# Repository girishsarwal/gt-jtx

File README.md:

# gt-jtx
What is gt-jtx?
I feel it's cool to control an airplane with a 3d joystick rather than gimbals. It's intuitive and real aircraft pilots (or those trained on MSFS) can appreciate. See Yoke and HOTAS ("Hotass")

After a good amount of self provocation, I embarked on the journey of doing a joystick based 4 analog and 1 digital channels transmitter for controlling Airplanes. Additionally, this system needs to have a basic menu system, settings (Expo/Dr, Rev etc..) and a monitor

# How does it work?
The gt-jtx uses a 3d joystick for controlling an RC airplane. The X axis map to ailerons (roll), Y to Elevator (pitch) and the joystick grip twist/Z axis map to Rudder (Yaw) control. The throttle control has a separate pot on the base of the joystick. Digital push buttons 5-12 on the joystick base are trim switches for the four channels and pressing unique combos on these switches along with power switch navigates through the menu and settings screen.

# Variants
There are three variants of the gt-jtx in order of ease of development

- Arduino Mega - V1.2 available - Open TX
- ATMEGA 8 - V1.0 available - Custom firmware
- ATMEGA 32 - Work under progress

See the wiki for more details

# Disclaimer
I take no responsibility or warranty for any damage to you or your equipment, that may arise out of or is a consequence of using or reproducing any parts or features of the gt-jtx software/hardware system. Everything you do is completely at your own risk and expense.

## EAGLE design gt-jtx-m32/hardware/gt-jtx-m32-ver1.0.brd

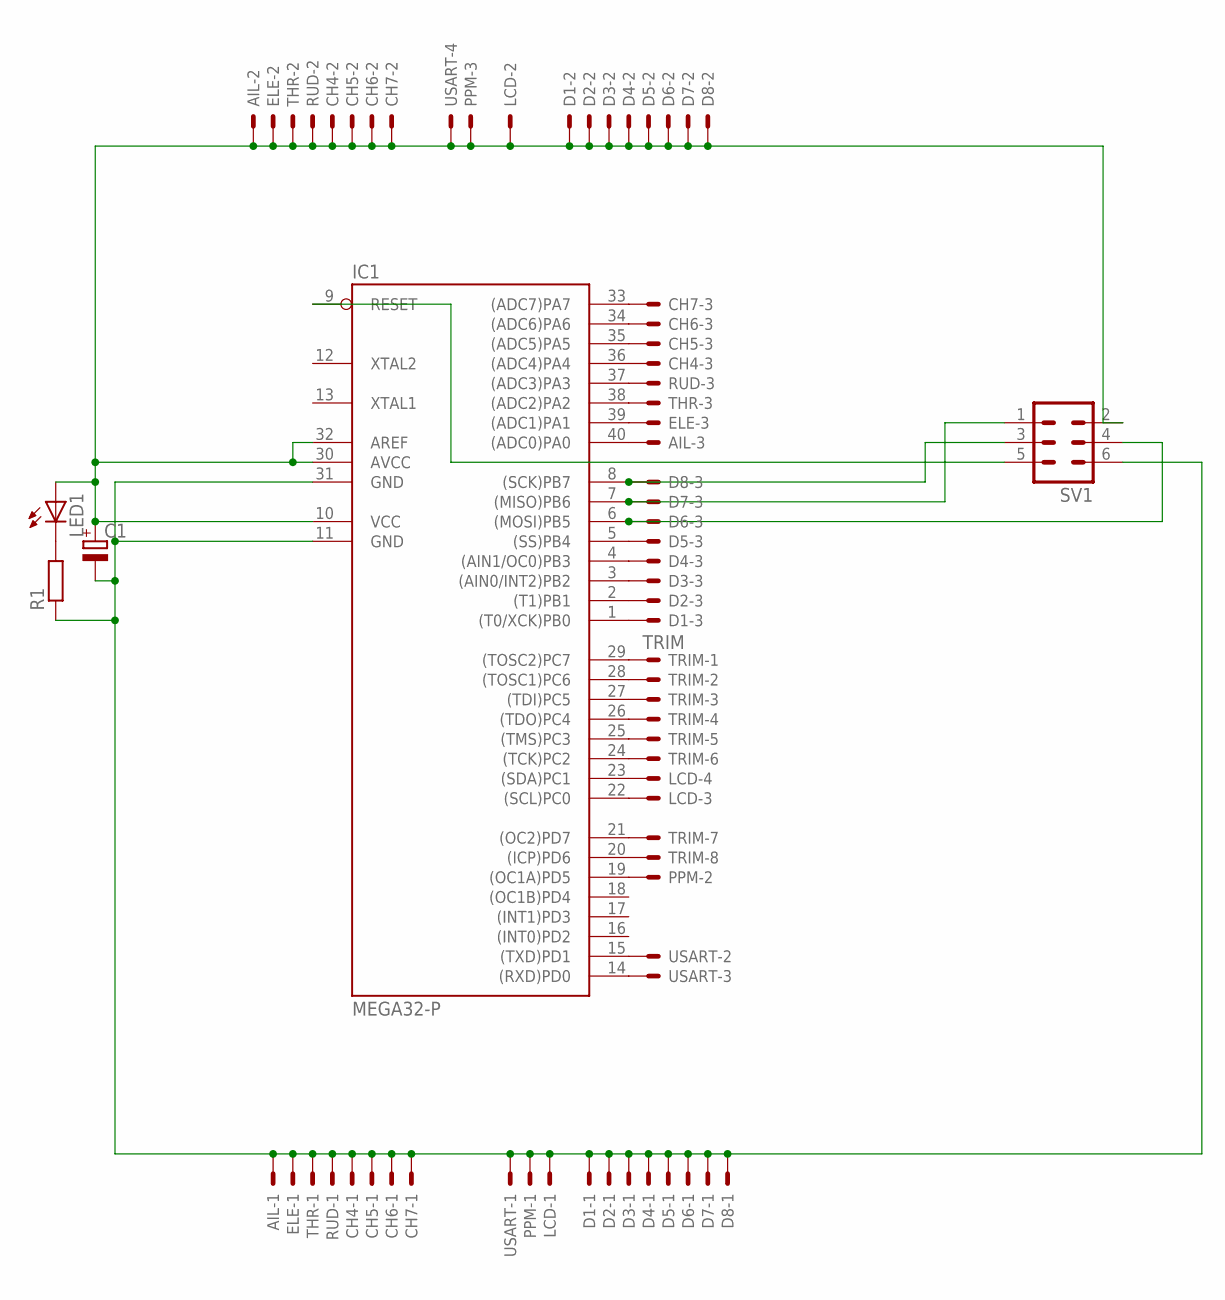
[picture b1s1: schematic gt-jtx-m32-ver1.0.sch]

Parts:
AIL: JST-XH-03-PIN-LONG-PAD; JST-XH-03-PACKAGE-LONG-PAD
C1: CPOL-EUC; PANASONIC_C
CH4, CH5, CH6, CH7: JST-XH-03-PIN-LONG-PAD; JST-XH-03-PACKAGE-LONG-PAD
D1, D2, D3, D4, D5, D6, D7, D8: JST-XH-03-PIN-LONG-PAD; JST-XH-03-PACKAGE-LONG-PAD
ELE: JST-XH-03-PIN-LONG-PAD; JST-XH-03-PACKAGE-LONG-PAD
IC1: MEGA32-P; DIL40
LCD: JST-XH-04-PIN-LONG-PAD; JST-XH-04-PACKAGE-LONG-PAD
LED1: LED5MM
PPM: JST-XH-03-PIN-LONG-PAD; JST-XH-03-PACKAGE-LONG-PAD
R1: R0204/7; 0204/7
RUD: JST-XH-03-PIN-LONG-PAD; JST-XH-03-PACKAGE-LONG-PAD
SV1: MA03-2
THR: JST-XH-03-PIN-LONG-PAD; JST-XH-03-PACKAGE-LONG-PAD
TRIM: TRIM; JST-XH-08-PACKAGE-LONG-PAD
USART: JST-XH-04-PIN-LONG-PAD; JST-XH-04-PACKAGE-LONG-PAD

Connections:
GND: AIL.1, C1.-, CH4.1, CH5.1, CH6.1, CH7.1, D1.1, D2.1, D3.1, D4.1, D5.1, D6.1, D7.1, D8.1, ELE.1, IC1.11 (GND), IC1.31 (GND), LCD.1, PPM.1, R1.1, RUD.1, SV1.6, THR.1, USART.1
unnamed: CH5.3, IC1.35 ((ADC5)PA5)
unnamed: CH6.3, IC1.34 ((ADC6)PA6)
unnamed: IC1.29 ((TOSC2)PC7), TRIM.1
unnamed: IC1.28 ((TOSC1)PC6), TRIM.2
unnamed: D1.3, IC1.1 ((T0/XCK)PB0)
unnamed: IC1.15 ((TXD)PD1), USART.2
unnamed: IC1.27 ((TDI)PC5), TRIM.3
unnamed: IC1.26 ((TDO)PC4), TRIM.4
unnamed: IC1.9 (RESET), SV1.5
unnamed: IC1.25 ((TMS)PC3), TRIM.5
unnamed: IC1.24 ((TCK)PC2), TRIM.6
unnamed: D6.3, IC1.6 ((MOSI)PB5), SV1.4
unnamed: D7.3, IC1.7 ((MISO)PB6), SV1.1
unnamed: D8.3, IC1.8 ((SCK)PB7), SV1.3
unnamed: D2.3, IC1.2 ((T1)PB1)
unnamed: IC1.21 ((OC2)PD7), TRIM.7
unnamed: IC1.20 ((ICP)PD6), TRIM.8
unnamed: IC1.14 ((RXD)PD0), USART.3
unnamed: IC1.23 ((SDA)PC1), LCD.4
unnamed: CH7.3, IC1.33 ((ADC7)PA7)
unnamed: CH4.3, IC1.36 ((ADC4)PA4)
unnamed: IC1.22 ((SCL)PC0), LCD.3
unnamed: IC1.19 ((OC1A)PD5), PPM.2
unnamed: D3.3, IC1.3 ((AIN0/INT2)PB2)
unnamed: D4.3, IC1.4 ((AIN1/OC0)PB3)
unnamed: D5.3, IC1.5 ((SS)PB4)
unnamed: IC1.37 ((ADC3)PA3), RUD.3
unnamed: IC1.38 ((ADC2)PA2), THR.3
unnamed: ELE.3, IC1.39 ((ADC1)PA1)
unnamed: AIL.3, IC1.40 ((ADC0)PA0)
unnamed: LED1.K (C), R1.2
VCC: AIL.2, C1.+, CH4.2, CH5.2, CH6.2, CH7.2, D1.2, D2.2, D3.2, D4.2, D5.2, D6.2, D7.2, D8.2, ELE.2, IC1.10 (VCC), IC1.30 (AVCC), IC1.32 (AREF), LCD.2, LED1.A, PPM.3, RUD.2, SV1.2, THR.2, USART.4

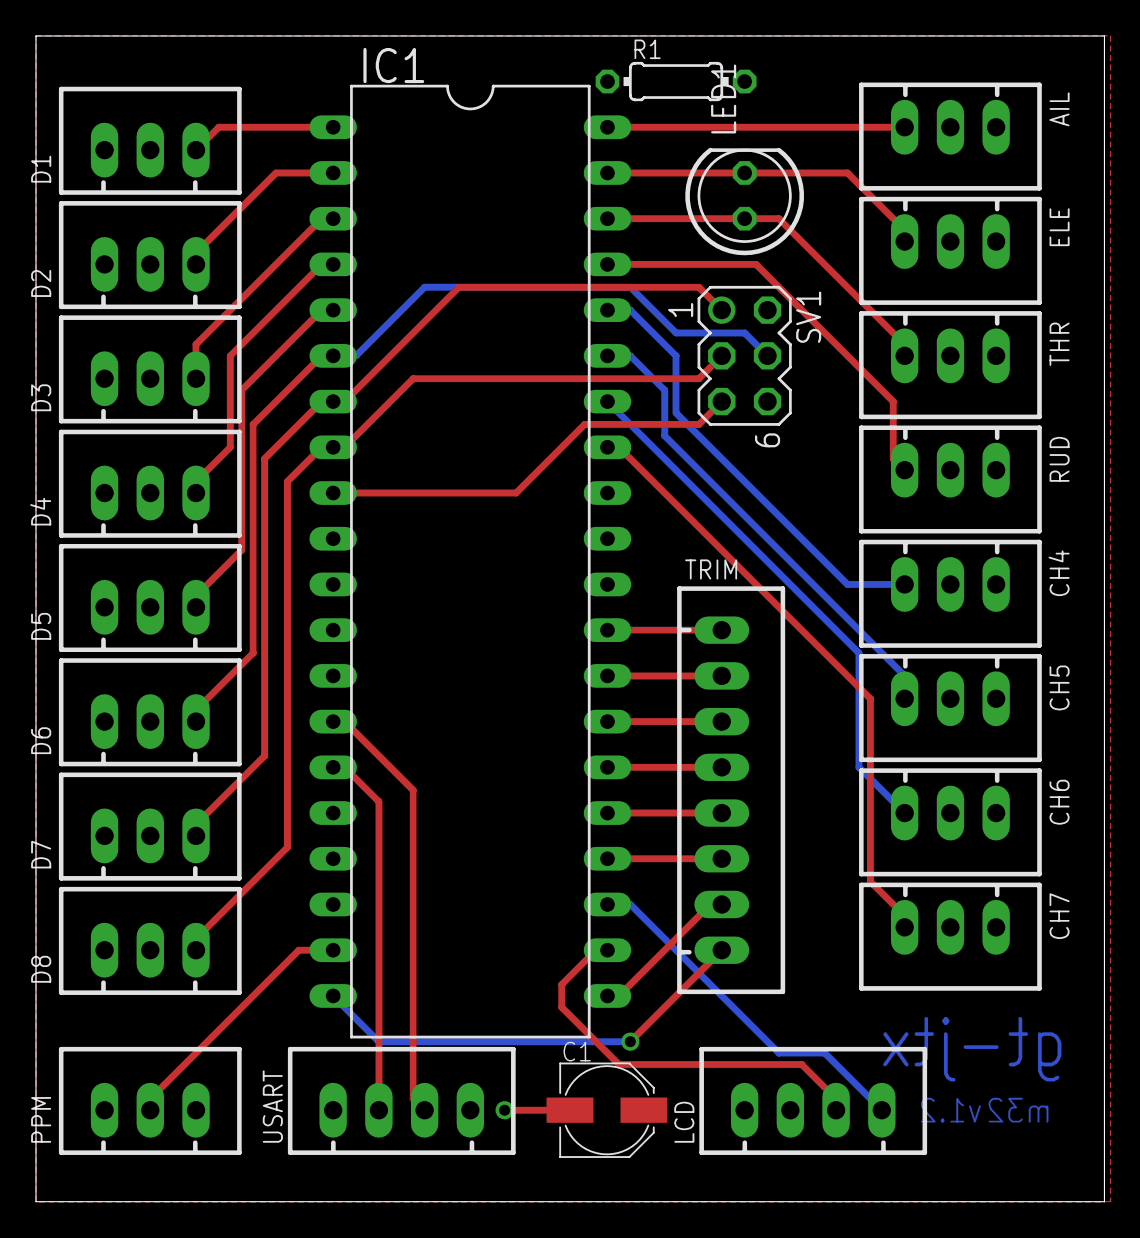
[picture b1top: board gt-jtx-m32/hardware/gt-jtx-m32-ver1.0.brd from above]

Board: 2 copper layers, 59.4 x 64.8 mm, 25 parts (0 on the bottom side), 33 nets.

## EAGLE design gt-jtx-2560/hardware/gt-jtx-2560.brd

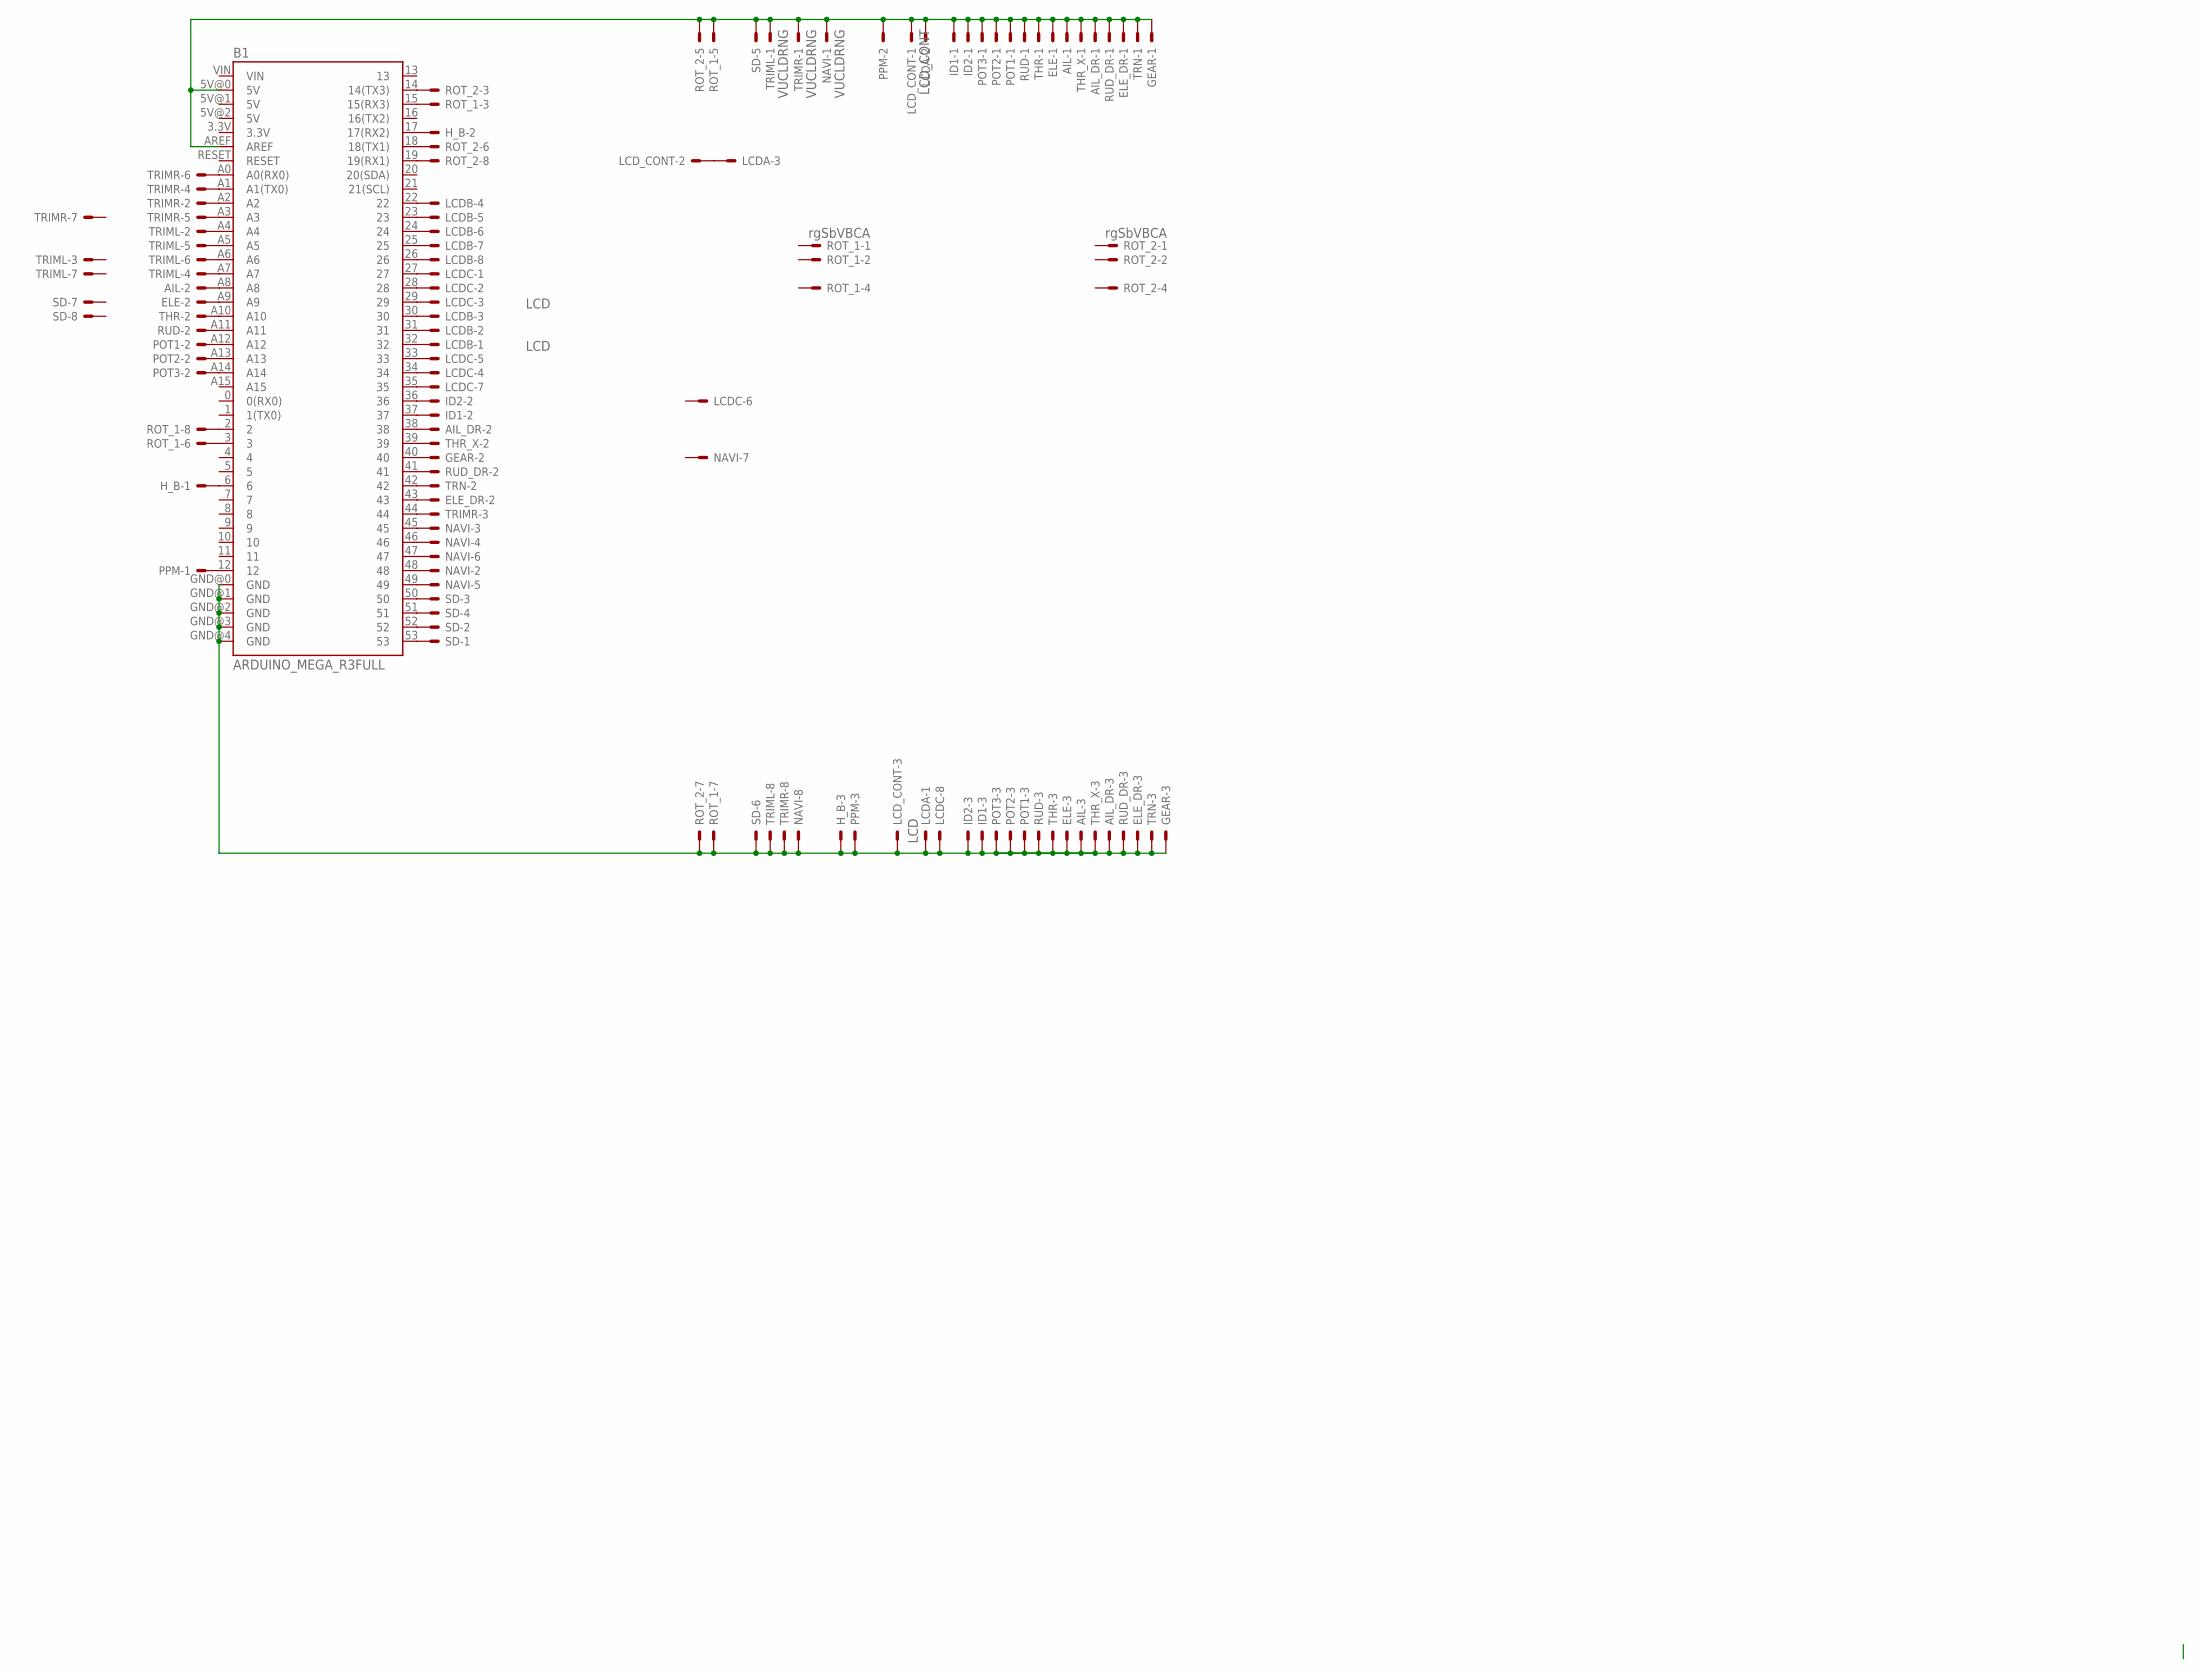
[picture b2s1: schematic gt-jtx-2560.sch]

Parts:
AIL: JST-XH-03-PIN-LONG-PAD; JST-XH-03-PACKAGE-LONG-PAD
AIL_DR: JST-XH-03-PIN-LONG-PAD; JST-XH-03-PACKAGE-LONG-PAD
B1: ARDUINO_MEGA_R3FULL; ARDUINO_MEGA
ELE: JST-XH-03-PIN-LONG-PAD; JST-XH-03-PACKAGE-LONG-PAD
ELE_DR: JST-XH-03-PIN-LONG-PAD; JST-XH-03-PACKAGE-LONG-PAD
GEAR: JST-XH-03-PIN-LONG-PAD; JST-XH-03-PACKAGE-LONG-PAD
H_B: JST-XH-03-PIN-LONG-PAD; JST-XH-03-PACKAGE-LONG-PAD
ID1, ID2: JST-XH-03-PIN-LONG-PAD; JST-XH-03-PACKAGE-LONG-PAD
LCDA: LCD; JST-XH-03-PACKAGE-LONG-PAD
LCDB: LCD; JST-XH-08-PACKAGE-LONG-PAD
LCDC: LCD; JST-XH-08-PACKAGE-LONG-PAD
LCD_CONT: LCD_CONT; JST-XH-03-PACKAGE-LONG-PAD
NAVI: VUCLDRNG; JST-XH-08-PACKAGE-LONG-PAD
POT1, POT2, POT3: JST-XH-03-PIN-LONG-PAD; JST-XH-03-PACKAGE-LONG-PAD
PPM: JST-XH-03-PIN-LONG-PAD; JST-XH-03-PACKAGE-LONG-PAD
ROT_1, ROT_2: rgSbVBCA; JST-XH-08-PACKAGE-LONG-PAD
RUD: JST-XH-03-PIN-LONG-PAD; JST-XH-03-PACKAGE-LONG-PAD
RUD_DR: JST-XH-03-PIN-LONG-PAD; JST-XH-03-PACKAGE-LONG-PAD
SD: JST-XH-08-PIN-LONG-PAD; JST-XH-08-PACKAGE-LONG-PAD
THR: JST-XH-03-PIN-LONG-PAD; JST-XH-03-PACKAGE-LONG-PAD
THR_X: JST-XH-03-PIN-LONG-PAD; JST-XH-03-PACKAGE-LONG-PAD
TRIML: VUCLDRNG; JST-XH-08-PACKAGE-LONG-PAD
TRIMR: VUCLDRNG; JST-XH-08-PACKAGE-LONG-PAD
TRN: JST-XH-03-PIN-LONG-PAD; JST-XH-03-PACKAGE-LONG-PAD

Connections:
GND: AIL.3, AIL_DR.3, B1.GND@0 (GND), B1.GND@1 (GND), B1.GND@2 (GND), B1.GND@3 (GND), B1.GND@4 (GND), ELE.3, ELE_DR.3, GEAR.3, H_B.3, ID1.3, ID2.3, LCDA.1, LCDC.8, LCD_CONT.3, NAVI.8, POT1.3, POT2.3, POT3.3, PPM.3, ROT_1.7, ROT_2.7, RUD.3, RUD_DR.3, SD.6, THR.3, THR_X.3, TRIML.8, TRIMR.8, TRN.3; also elsewhere on the board
unnamed: B1.22, LCDB.4
unnamed: B1.23, LCDB.5
unnamed: B1.24, LCDB.6
unnamed: B1.25, LCDB.7
unnamed: B1.26, LCDB.8
unnamed: B1.27, LCDC.1
unnamed: B1.28, LCDC.2
unnamed: B1.29, LCDC.3
unnamed: B1.48, NAVI.2
unnamed: B1.45, NAVI.3
unnamed: B1.46, NAVI.4
unnamed: B1.49, NAVI.5
unnamed: B1.47, NAVI.6
unnamed: B1.A2, TRIMR.2
unnamed: B1.A7, TRIML.4
unnamed: B1.53, SD.1
unnamed: B1.A5, TRIML.5
unnamed: B1.44, TRIMR.3
unnamed: AIL.2, B1.A8
unnamed: B1.A9, ELE.2
unnamed: B1.A10, THR.2
unnamed: B1.A11, RUD.2
unnamed: B1.A12, POT1.2
unnamed: B1.A13, POT2.2
unnamed: B1.A14, POT3.2
unnamed: B1.52, SD.2
unnamed: B1.A1 (A1(TX0)), TRIMR.4
unnamed: B1.A3, TRIMR.5
unnamed: B1.50, SD.3
unnamed: B1.51, SD.4
unnamed: B1.15 (15(RX3)), ROT_1.3
unnamed: B1.6, H_B.1
unnamed: B1.39, THR_X.2
unnamed: B1.41, RUD_DR.2
unnamed: B1.43, ELE_DR.2
unnamed: AIL_DR.2, B1.38
unnamed: B1.42, TRN.2
unnamed: B1.40, GEAR.2
unnamed: B1.17 (17(RX2)), H_B.2
unnamed: B1.A0 (A0(RX0)), TRIMR.6
unnamed: B1.30, LCDB.3
unnamed: B1.31, LCDB.2
unnamed: B1.A6, TRIML.6
unnamed: B1.A4, TRIML.2
unnamed: B1.14 (14(TX3)), ROT_2.3
unnamed: B1.2, ROT_1.8
unnamed: B1.3, ROT_1.6
unnamed: B1.19 (19(RX1)), ROT_2.8
unnamed: B1.18 (18(TX1)), ROT_2.6
unnamed: B1.32, LCDB.1
unnamed: B1.34, LCDC.4
unnamed: B1.33, LCDC.5
unnamed: B1.35, LCDC.7
unnamed: LCDA.3, LCD_CONT.2
unnamed: B1.36, ID2.2
unnamed: B1.37, ID1.2
VCC: AIL.1, AIL_DR.1, B1.5V@0 (5V), B1.AREF, ELE.1, ELE_DR.1, GEAR.1, ID1.1, ID2.1, LCDA.2, LCD_CONT.1, NAVI.1, POT1.1, POT2.1, POT3.1, PPM.2, ROT_1.5, ROT_2.5, RUD.1, RUD_DR.1, SD.5, THR.1, THR_X.1, TRIML.1, TRIMR.1, TRN.1

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
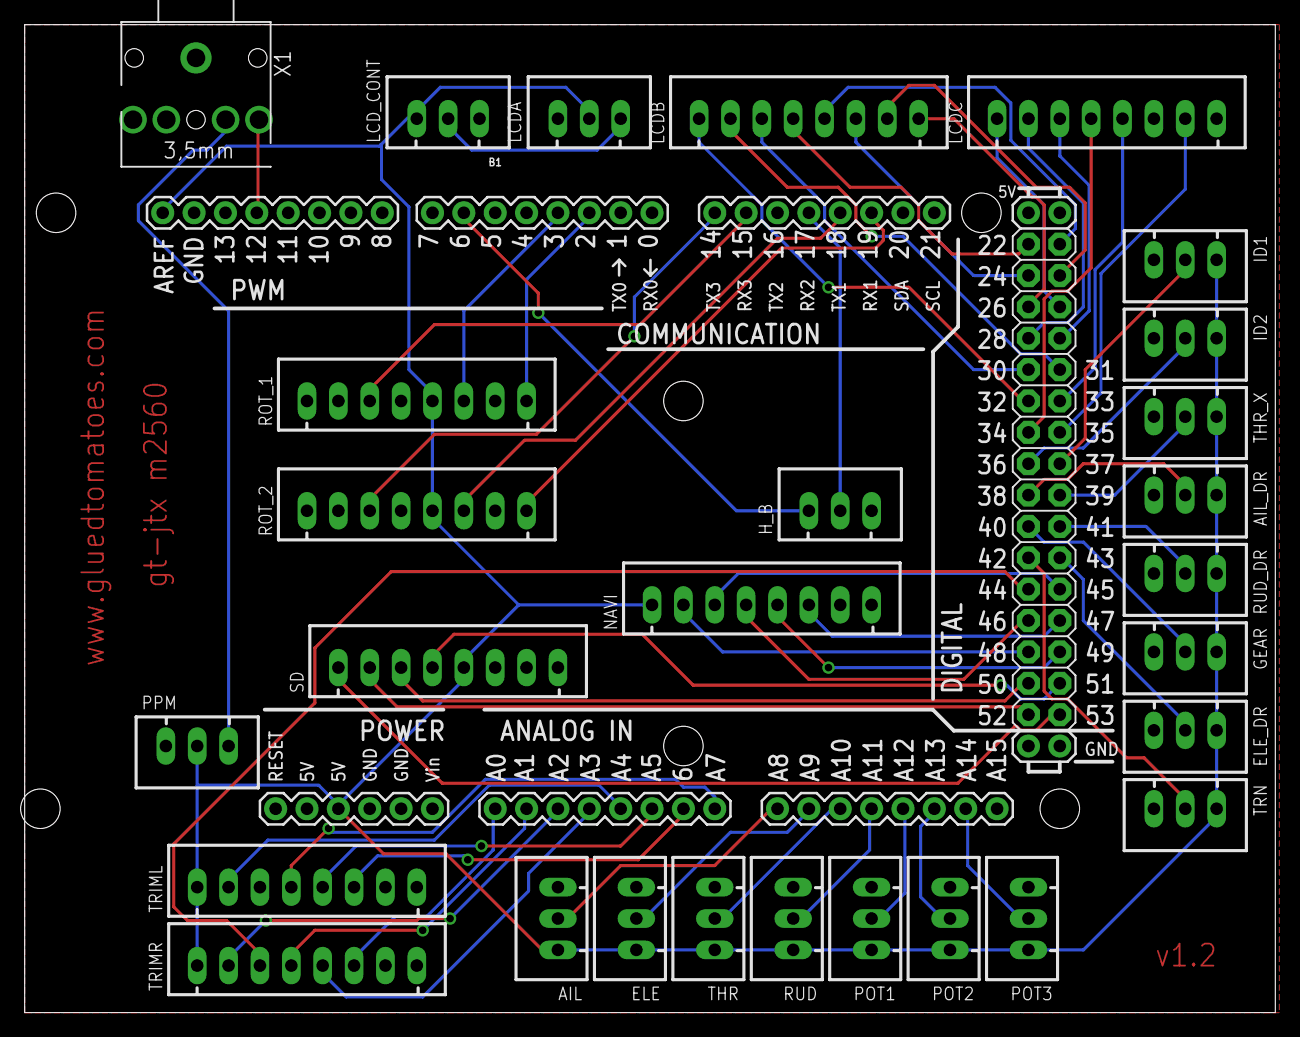
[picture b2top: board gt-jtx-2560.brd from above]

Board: 2 copper layers, 101.3 x 80.0 mm, 29 parts (0 on the bottom side), 60 nets.

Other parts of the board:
X1: SIM; STX3100

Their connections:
GND: X1.1; also elsewhere on the board

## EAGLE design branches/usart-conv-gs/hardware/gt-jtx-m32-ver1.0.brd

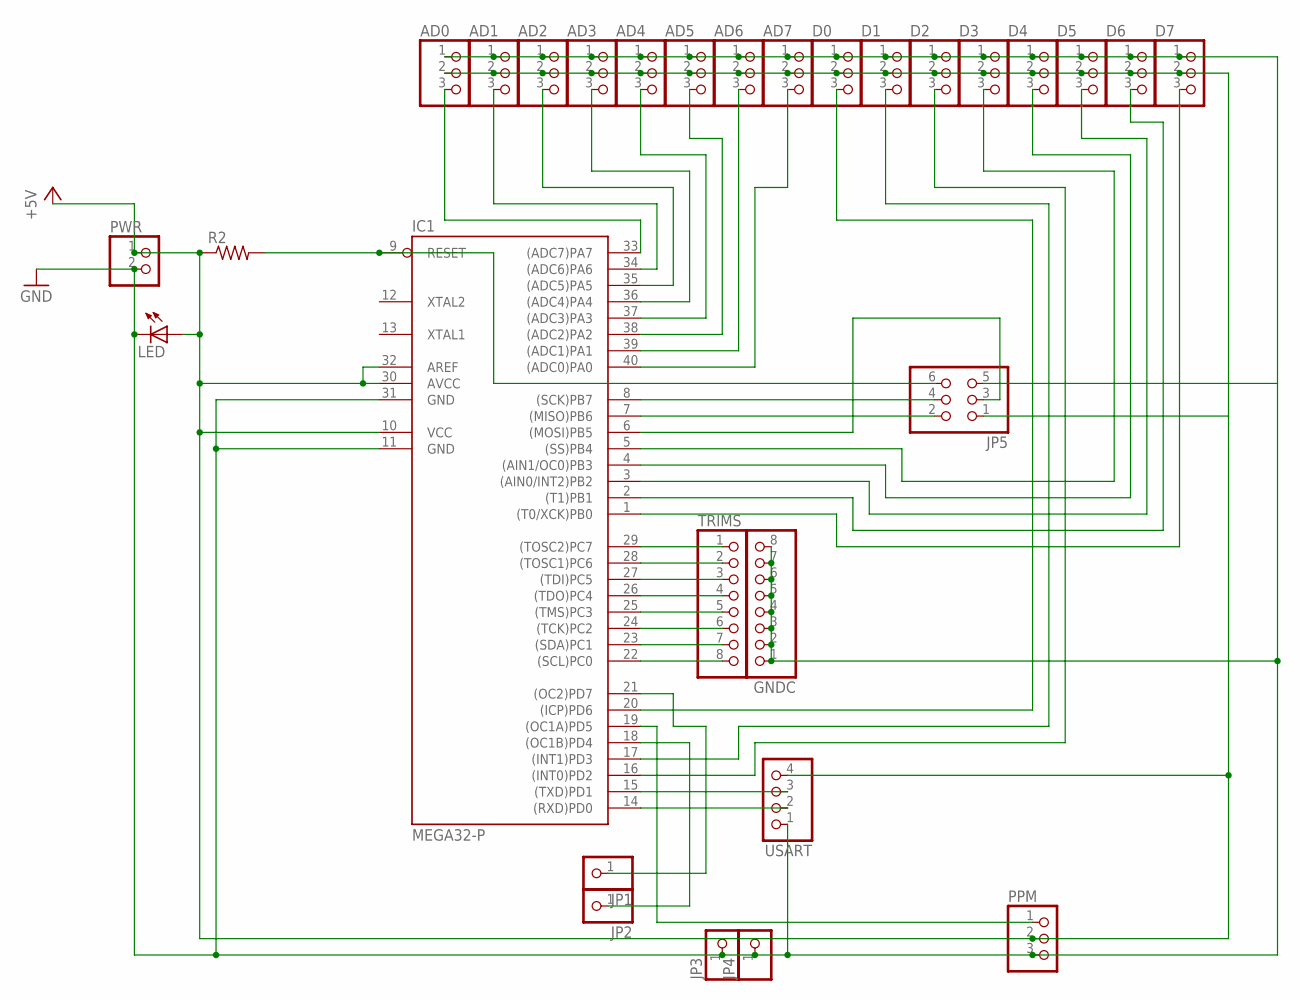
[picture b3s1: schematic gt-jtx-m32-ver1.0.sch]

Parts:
AD0, AD1, AD2, AD3, AD4, AD5, AD6, AD7: PINHD-1X3; 1X03
D0, D1, D2, D3, D4, D5, D6, D7: PINHD-1X3; 1X03
GNDC: PINHD-1X8; 1X08
IC1: MEGA32-P; DIL40
JP1, JP2, JP3, JP4: PINHD-1X1; 1X01
JP5: PINHD-2X3; 2X03
LED: LED5MM
PPM: PINHD-1X3; 1X03
PWR: PINHD-1X2; 1X02
R2: R-US_0204/2V; 0204V
TRIMS: PINHD-1X8; 1X08
USART: PINHD-1X4; 1X04

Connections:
+5V: AD0.2, AD1.2, AD2.2, AD3.2, AD4.2, AD5.2, AD6.2, AD7.2, D0.2, D1.2, D2.2, D3.2, D4.2, D5.2, D6.2, D7.2, IC1.10 (VCC), IC1.30 (AVCC), IC1.32 (AREF), JP5.1, LED.A, PPM.2, PWR.1, R2.1, USART.4
GND: AD0.1, AD1.1, AD2.1, AD3.1, AD4.1, AD5.1, AD6.1, AD7.1, D0.1, D1.1, D2.1, D3.1, D4.1, D5.1, D6.1, D7.1, GNDC.1, GNDC.2, GNDC.3, GNDC.4, GNDC.5, GNDC.6, GNDC.7, GNDC.8, IC1.11 (GND), IC1.31 (GND), JP3.1, JP4.1, JP5.5, LED.K (C), PPM.3, PWR.2, USART.1
unnamed: AD7.3, IC1.40 ((ADC0)PA0)
unnamed: AD6.3, IC1.39 ((ADC1)PA1)
unnamed: AD5.3, IC1.38 ((ADC2)PA2)
unnamed: AD4.3, IC1.37 ((ADC3)PA3)
unnamed: IC1.14 ((RXD)PD0), USART.2
unnamed: IC1.15 ((TXD)PD1), USART.3
unnamed: IC1.29 ((TOSC2)PC7), TRIMS.1
unnamed: AD3.3, IC1.36 ((ADC4)PA4)
unnamed: IC1.9 (RESET), JP5.6, R2.2
unnamed: AD2.3, IC1.35 ((ADC5)PA5)
unnamed: AD1.3, IC1.34 ((ADC6)PA6)
unnamed: IC1.6 ((MOSI)PB5), JP5.3
unnamed: IC1.7 ((MISO)PB6), JP5.2
unnamed: IC1.8 ((SCK)PB7), JP5.4
unnamed: IC1.19 ((OC1A)PD5), PPM.1
unnamed: IC1.28 ((TOSC1)PC6), TRIMS.2
unnamed: AD0.3, IC1.33 ((ADC7)PA7)
unnamed: IC1.27 ((TDI)PC5), TRIMS.3
unnamed: IC1.26 ((TDO)PC4), TRIMS.4
unnamed: IC1.25 ((TMS)PC3), TRIMS.5
unnamed: IC1.24 ((TCK)PC2), TRIMS.6
unnamed: IC1.23 ((SDA)PC1), TRIMS.7
unnamed: IC1.22 ((SCL)PC0), TRIMS.8
unnamed: D3.3, IC1.5 ((SS)PB4)
unnamed: D4.3, IC1.4 ((AIN1/OC0)PB3)
unnamed: D5.3, IC1.3 ((AIN0/INT2)PB2)
unnamed: D6.3, IC1.2 ((T1)PB1)
unnamed: D7.3, IC1.1 ((T0/XCK)PB0)
unnamed: D2.3, IC1.16 ((INT0)PD2)
unnamed: D1.3, IC1.17 ((INT1)PD3)
unnamed: D0.3, IC1.20 ((ICP)PD6)
unnamed: IC1.18 ((OC1B)PD4), JP2.1
unnamed: IC1.21 ((OC2)PD7), JP1.1

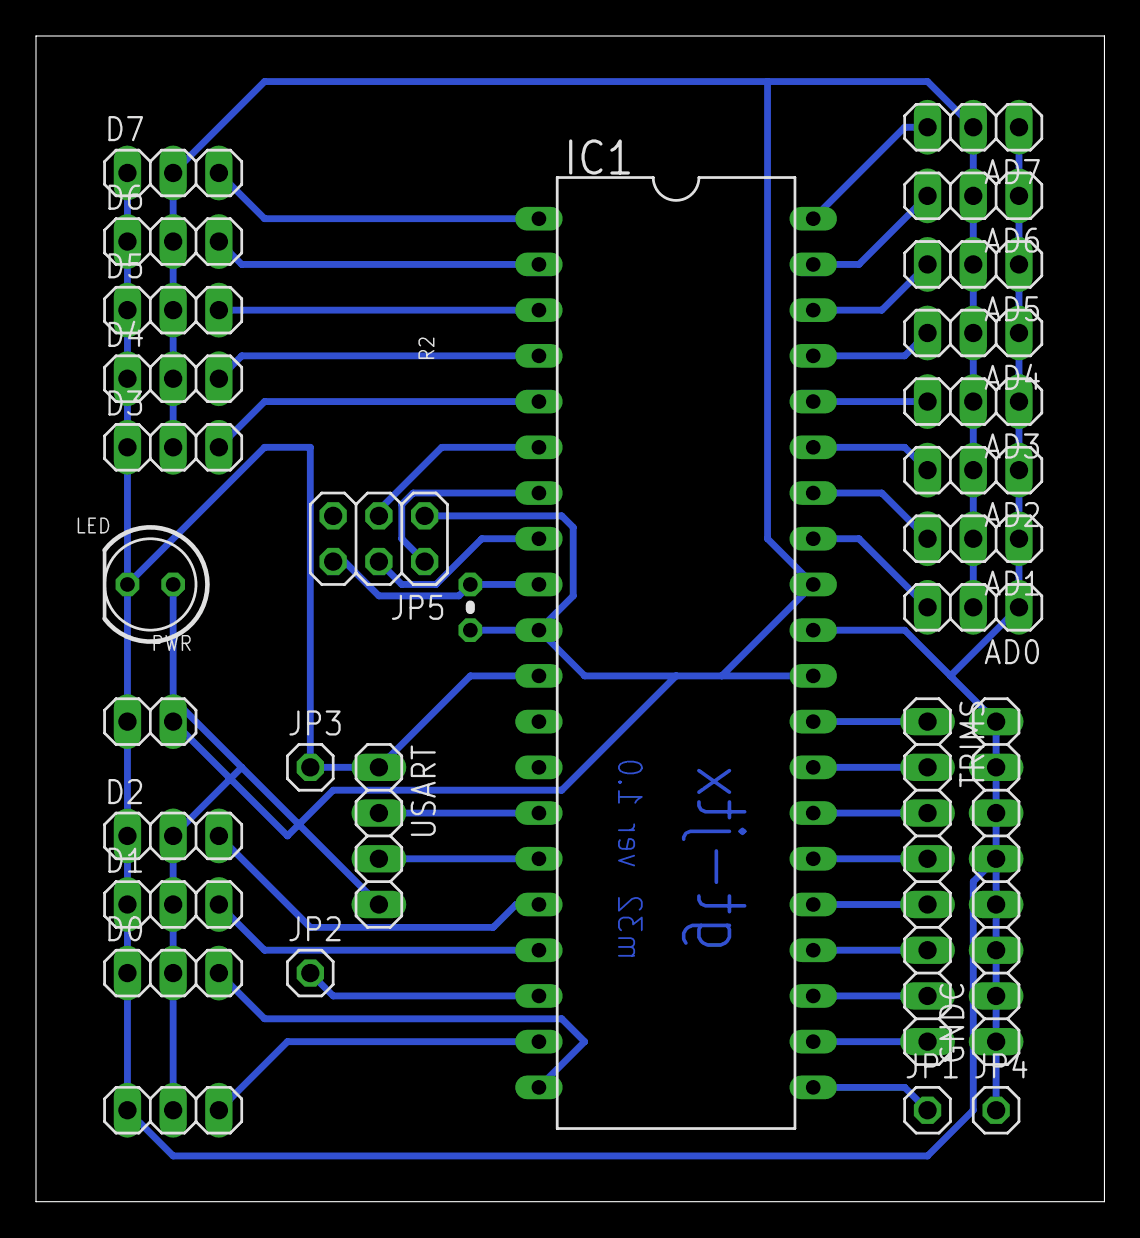
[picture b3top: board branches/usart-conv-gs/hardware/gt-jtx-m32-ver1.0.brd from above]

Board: 2 copper layers, 59.4 x 64.8 mm, 29 parts (0 on the bottom side), 35 nets.

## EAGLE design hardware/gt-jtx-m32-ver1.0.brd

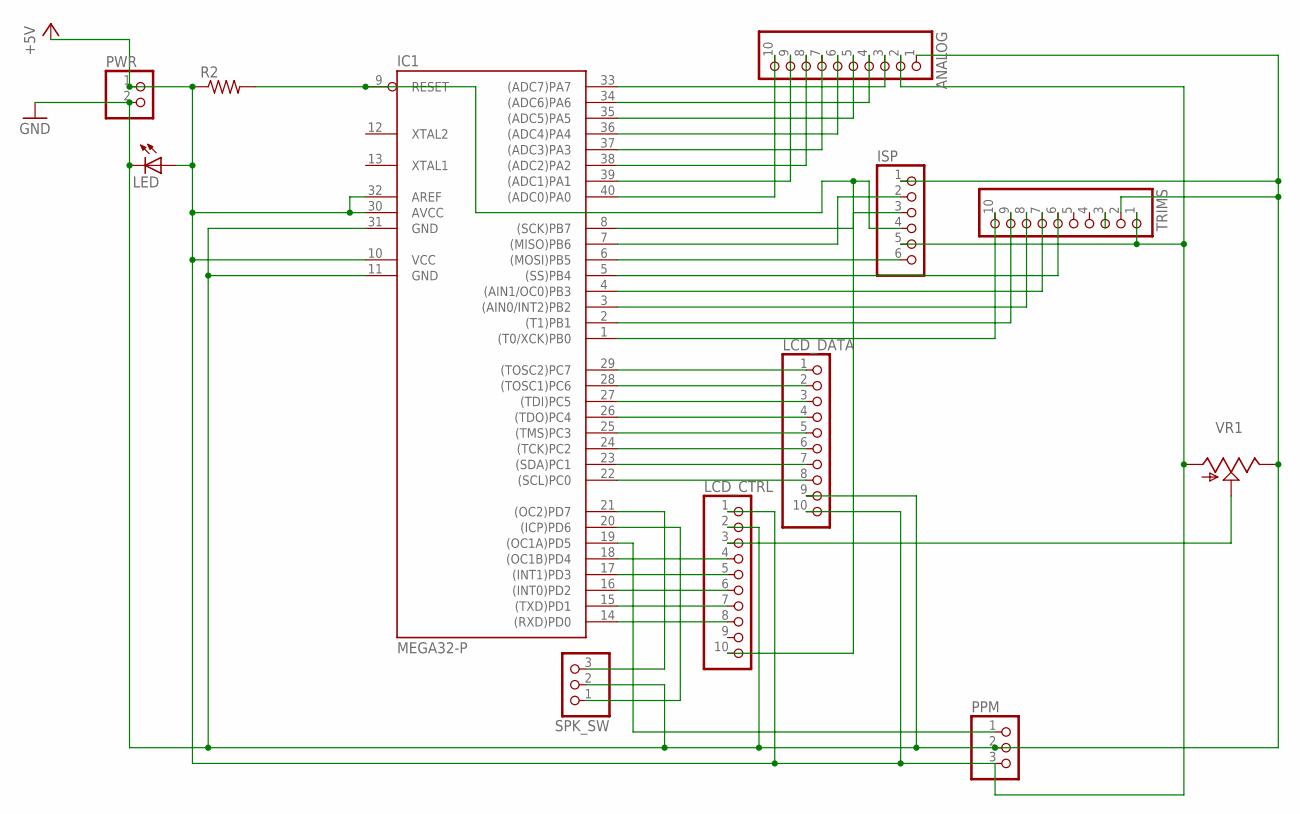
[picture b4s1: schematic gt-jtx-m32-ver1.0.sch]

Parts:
ANALOG: PINHD-1X10; 1X10
IC1: MEGA32-P; DIL40
ISP: PINHD-1X6; 1X06
LCD_CTRL: PINHD-1X10; 1X10
LCD_DATA: PINHD-1X10; 1X10
LED: LED5MM
PPM: PINHD-1X3; 1X03
PWR: PINHD-1X2; 1X02
R2: R-US_0204/2V; 0204V
SPK_SW: PINHD-1X3; 1X03
TRIMS: PINHD-1X10; 1X10
VR1: TRIM_US-CA6V; CA6V

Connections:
+5V: ANALOG.2, IC1.10 (VCC), IC1.30 (AVCC), IC1.32 (AREF), ISP.5, LCD_CTRL.1, LCD_DATA.10, LED.A, PPM.3, PWR.1, R2.1, TRIMS.1, VR1.A
CONTRA_ADJ: LCD_CTRL.3, VR1.S
CS1: IC1.17 ((INT1)PD3), LCD_CTRL.5
CS2: IC1.18 ((OC1B)PD4), LCD_CTRL.4
D0: IC1.22 ((SCL)PC0), LCD_DATA.8
D1: IC1.23 ((SDA)PC1), LCD_DATA.7
D2: IC1.24 ((TCK)PC2), LCD_DATA.6
D3: IC1.25 ((TMS)PC3), LCD_DATA.5
D4: IC1.26 ((TDO)PC4), LCD_DATA.4
D5: IC1.27 ((TDI)PC5), LCD_DATA.3
D6: IC1.28 ((TOSC1)PC6), LCD_DATA.2
D7: IC1.29 ((TOSC2)PC7), LCD_DATA.1
E: IC1.16 ((INT0)PD2), LCD_CTRL.6
GND: ANALOG.1, IC1.11 (GND), IC1.31 (GND), ISP.1, LCD_CTRL.2, LCD_DATA.9, LED.K (C), PPM.2, PWR.2, SPK_SW.2, TRIMS.2, VR1.E
unnamed: ANALOG.10, IC1.40 ((ADC0)PA0)
unnamed: ANALOG.9, IC1.39 ((ADC1)PA1)
unnamed: ANALOG.8, IC1.38 ((ADC2)PA2)
unnamed: ANALOG.7, IC1.37 ((ADC3)PA3)
unnamed: IC1.20 ((ICP)PD6), SPK_SW.1
unnamed: IC1.21 ((OC2)PD7), SPK_SW.3
unnamed: ANALOG.6, IC1.36 ((ADC4)PA4)
unnamed: IC1.9 (RESET), ISP.4, LCD_CTRL.10, R2.2
unnamed: ANALOG.5, IC1.35 ((ADC5)PA5)
unnamed: ANALOG.4, IC1.34 ((ADC6)PA6)
unnamed: IC1.6 ((MOSI)PB5), ISP.6
unnamed: IC1.7 ((MISO)PB6), ISP.2
unnamed: IC1.8 ((SCK)PB7), ISP.3
unnamed: IC1.19 ((OC1A)PD5), PPM.1
unnamed: ANALOG.3, IC1.33 ((ADC7)PA7)
unnamed: IC1.1 ((T0/XCK)PB0), TRIMS.10
unnamed: IC1.2 ((T1)PB1), TRIMS.9
unnamed: IC1.3 ((AIN0/INT2)PB2), TRIMS.8
unnamed: IC1.4 ((AIN1/OC0)PB3), TRIMS.7
unnamed: IC1.5 ((SS)PB4), TRIMS.6
RS: IC1.14 ((RXD)PD0), LCD_CTRL.8
RW: IC1.15 ((TXD)PD1), LCD_CTRL.7

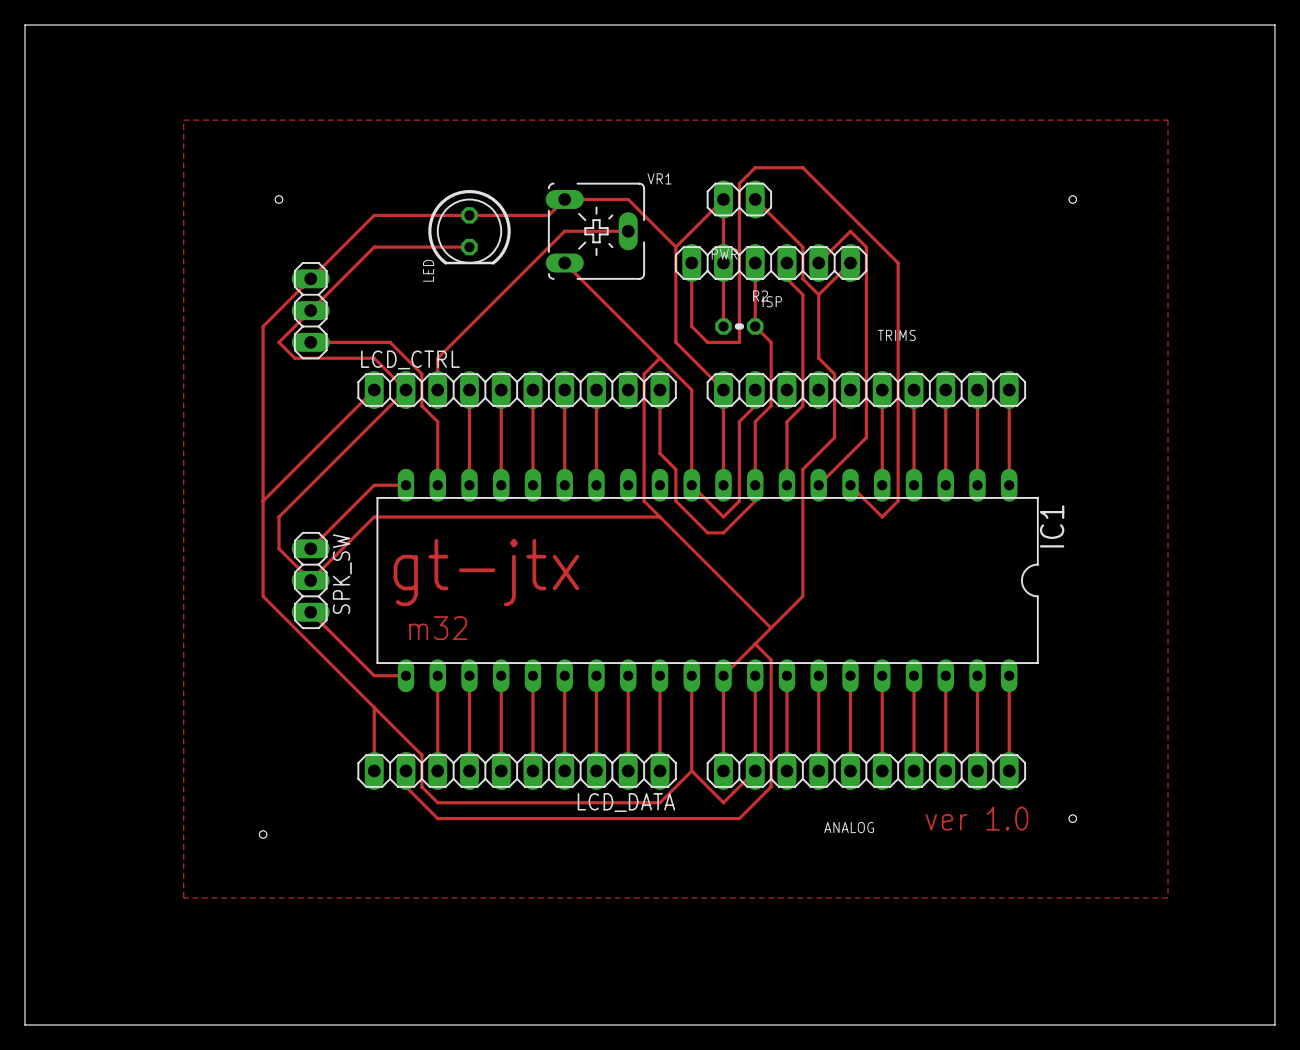
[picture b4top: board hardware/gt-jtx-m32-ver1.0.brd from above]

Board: 2 copper layers, 100.0 x 80.0 mm, 12 parts (0 on the bottom side), 36 nets.

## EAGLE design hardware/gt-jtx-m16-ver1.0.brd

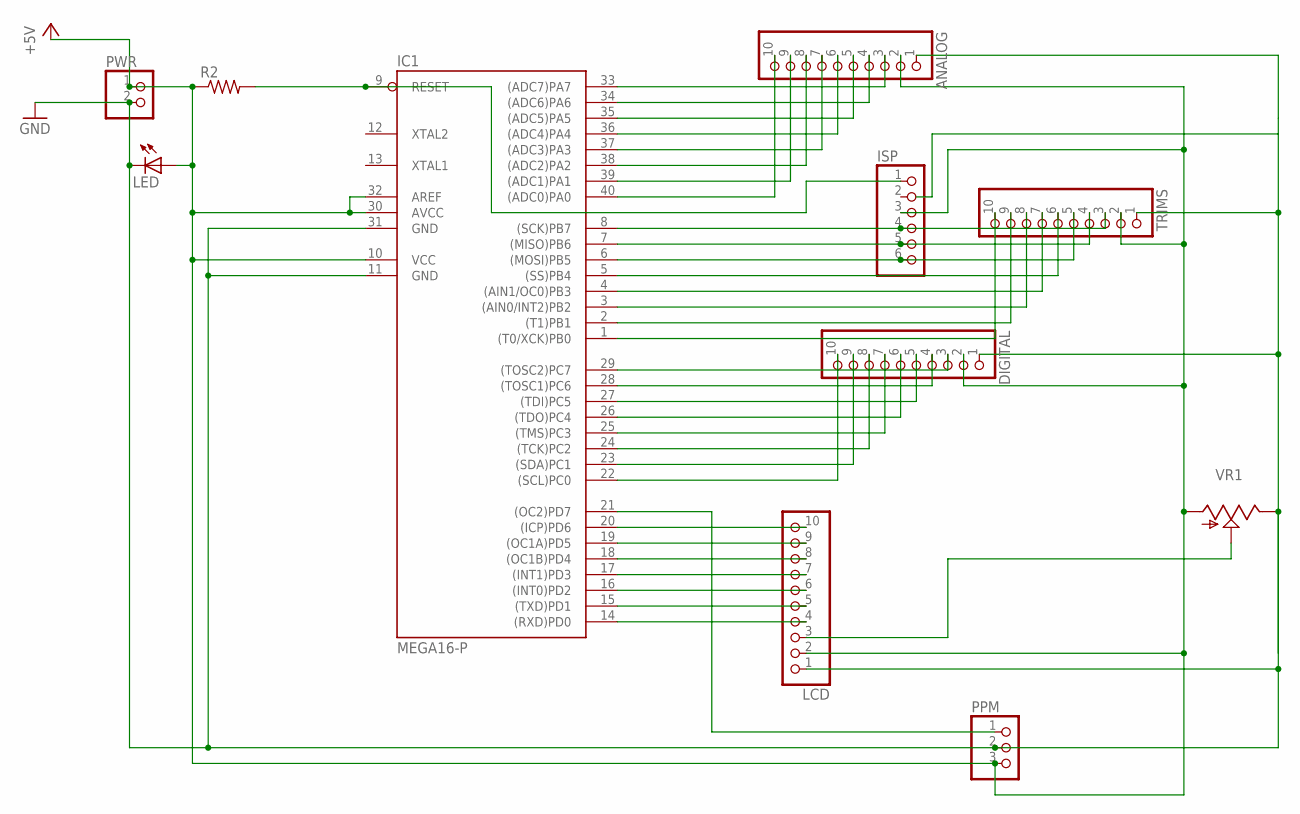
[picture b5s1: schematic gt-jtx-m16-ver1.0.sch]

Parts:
ANALOG: PINHD-1X10; 1X10
DIGITAL: PINHD-1X10; 1X10
IC1: MEGA16-P; DIL40
ISP: PINHD-1X6; 1X06
LCD: PINHD-1X10; 1X10
LED: LED5MM
PPM: PINHD-1X3; 1X03
PWR: PINHD-1X2; 1X02
R2: R-US_0204/2V; 0204V
TRIMS: PINHD-1X10; 1X10
VR1: TRIM_US-CA6V; CA6V

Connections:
+5V: ANALOG.2, DIGITAL.2, IC1.30 (AVCC), IC1.32 (AREF), ISP.3, LCD.2, LED.A, PPM.3, PWR.1, R2.1, TRIMS.2, VR1.A
GND: ANALOG.1, DIGITAL.1, IC1.11 (GND), IC1.31 (GND), LCD.1, LED.K (C), PPM.2, PWR.2, TRIMS.1, VR1.E
unnamed: ANALOG.10, IC1.40 ((ADC0)PA0)
unnamed: ANALOG.9, IC1.39 ((ADC1)PA1)
unnamed: ANALOG.8, IC1.38 ((ADC2)PA2)
unnamed: ANALOG.7, IC1.37 ((ADC3)PA3)
unnamed: IC1.20 ((ICP)PD6), LCD.10
unnamed: IC1.19 ((OC1A)PD5), LCD.9
unnamed: IC1.18 ((OC1B)PD4), LCD.8
unnamed: ANALOG.6, IC1.36 ((ADC4)PA4)
unnamed: LCD.3, VR1.S
unnamed: ANALOG.5, IC1.35 ((ADC5)PA5)
unnamed: ANALOG.4, IC1.34 ((ADC6)PA6)
unnamed: IC1.17 ((INT1)PD3), LCD.7
unnamed: IC1.16 ((INT0)PD2), LCD.6
unnamed: IC1.15 ((TXD)PD1), LCD.5
unnamed: IC1.14 ((RXD)PD0), LCD.4
unnamed: IC1.21 ((OC2)PD7), PPM.1
unnamed: ANALOG.3, IC1.33 ((ADC7)PA7)
unnamed: DIGITAL.3, IC1.29 ((TOSC2)PC7)
unnamed: DIGITAL.4, IC1.28 ((TOSC1)PC6)
unnamed: DIGITAL.5, IC1.27 ((TDI)PC5)
unnamed: DIGITAL.6, IC1.26 ((TDO)PC4)
unnamed: DIGITAL.7, IC1.25 ((TMS)PC3)
unnamed: DIGITAL.8, IC1.24 ((TCK)PC2)
unnamed: DIGITAL.9, IC1.23 ((SDA)PC1)
unnamed: IC1.9 (RESET), ISP.1, R2.2
unnamed: DIGITAL.10, IC1.22 ((SCL)PC0)
unnamed: IC1.1 ((T0/XCK)PB0), TRIMS.10
unnamed: IC1.8 ((SCK)PB7), ISP.4, TRIMS.3
unnamed: IC1.2 ((T1)PB1), TRIMS.9
unnamed: IC1.3 ((AIN0/INT2)PB2), TRIMS.8
unnamed: IC1.4 ((AIN1/OC0)PB3), TRIMS.7
unnamed: IC1.5 ((SS)PB4), TRIMS.6
unnamed: IC1.6 ((MOSI)PB5), ISP.6, TRIMS.5
unnamed: IC1.7 ((MISO)PB6), ISP.5, TRIMS.4
VCC: IC1.10 (VCC)

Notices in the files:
parts and their libraries:
SparkFun-Boards: Licensing: Creative Commons ShareAlike 4.0 International - https://creativecommons.org/licenses/by-sa/4.0
